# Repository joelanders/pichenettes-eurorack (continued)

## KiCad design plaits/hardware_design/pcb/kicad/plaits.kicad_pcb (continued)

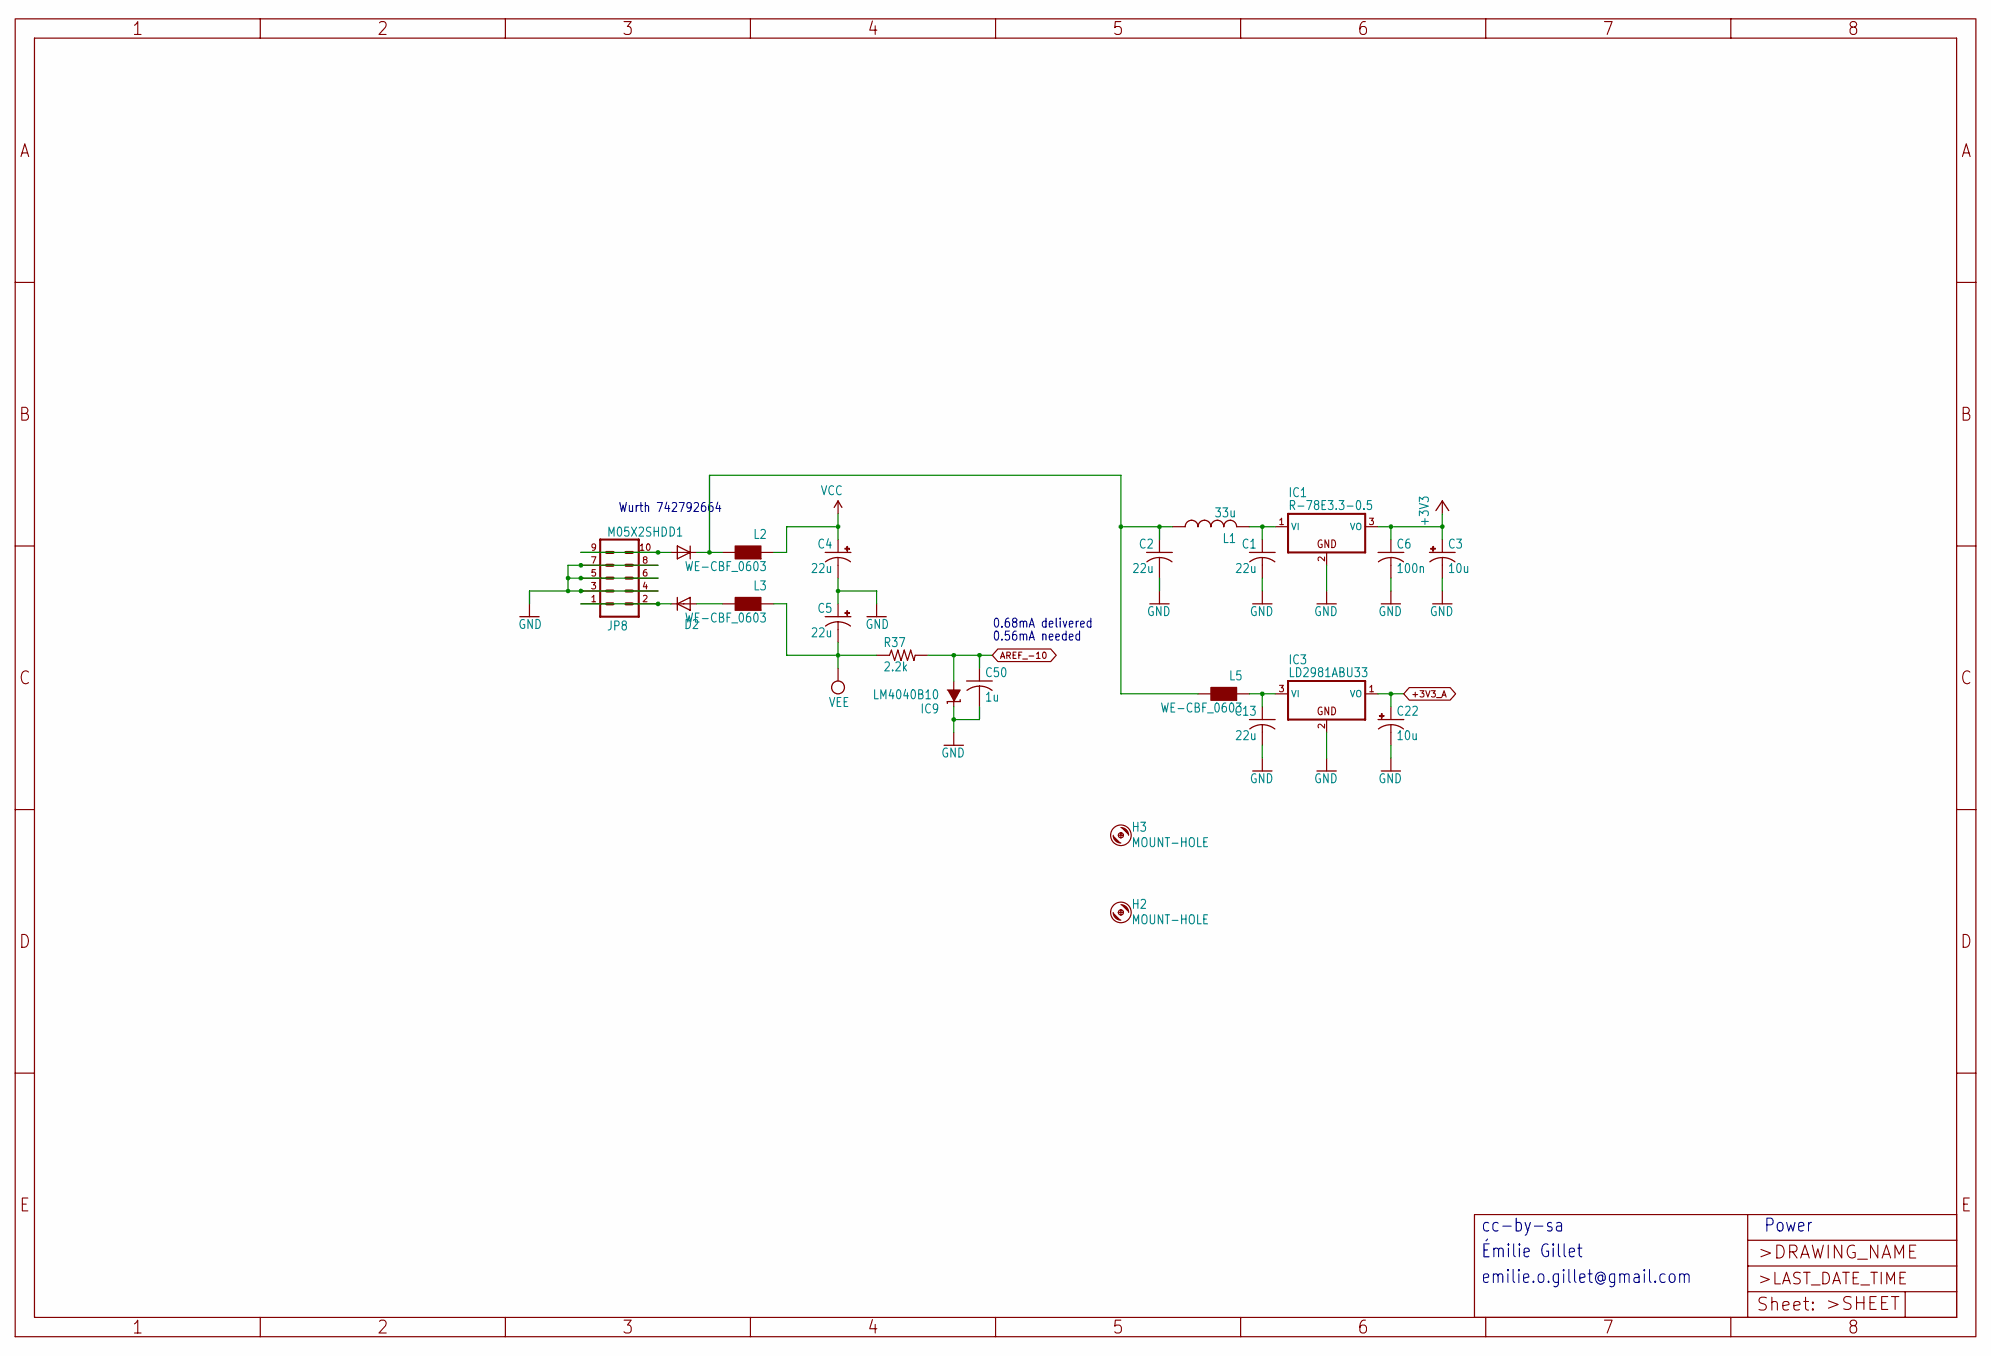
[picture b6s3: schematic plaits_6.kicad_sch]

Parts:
C1, C2, C13: 22u; C1206
C3, C22: 10u; PANASONIC_B
C4, C5: 22u; PANASONIC_B
C6: 100n; C0402
C50: 1u; C0402
D1, D2: 1N5819HW; SOD123
H2, H3: MOUNT-HOLE; 3,0TINY
IC1: R-78E3.3-0.5; WE78
IC3: LD2981ABU33; SOT89
IC9: LM4040B10; DBZ_R-PDSO-G3
JP8: M05X2SHD; 2X5-SHROUDED
L1: 33u; L2012C
L2, L3, L5: WE-CBF_0603; 0603
R37: 2.2k; R0402

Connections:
+3V3: C3.+, C6.1, IC1.3 (VO); also elsewhere on the board
+3V3_A: C22.+, IC3.1 (VO); also elsewhere on the board
AREF_-10: C50.1, IC9.2 (A), R37.2; also elsewhere on the board
GND: C1.2, C2.2, C3.-, C4.-, C5.+, C6.2, C13.2, C22.-, C50.2, IC1.2 (GND), IC3.2 (GND), IC9.1 (C), JP8.3, JP8.4, JP8.5, JP8.6, JP8.7, JP8.8; also elsewhere on the board
unnamed: C2.1, D1.C, L1.1, L2.2, L5.2
unnamed: D1.A, JP8.9, JP8.10
unnamed: D2.A, L3.2
unnamed: D2.C, JP8.1, JP8.2
unnamed: C1.1, IC1.1 (VI), L1.2
unnamed: C13.1, IC3.3 (VI), L5.1
VCC: C4.+, L2.1; also elsewhere on the board
VEE: C5.-, L3.1, R37.1; also elsewhere on the board

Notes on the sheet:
Émilie Gillet
0.56mA needed
Power
0.68mA delivered
emilie.o.gillet@gmail.com
Wurth 742792664
cc-by-sa

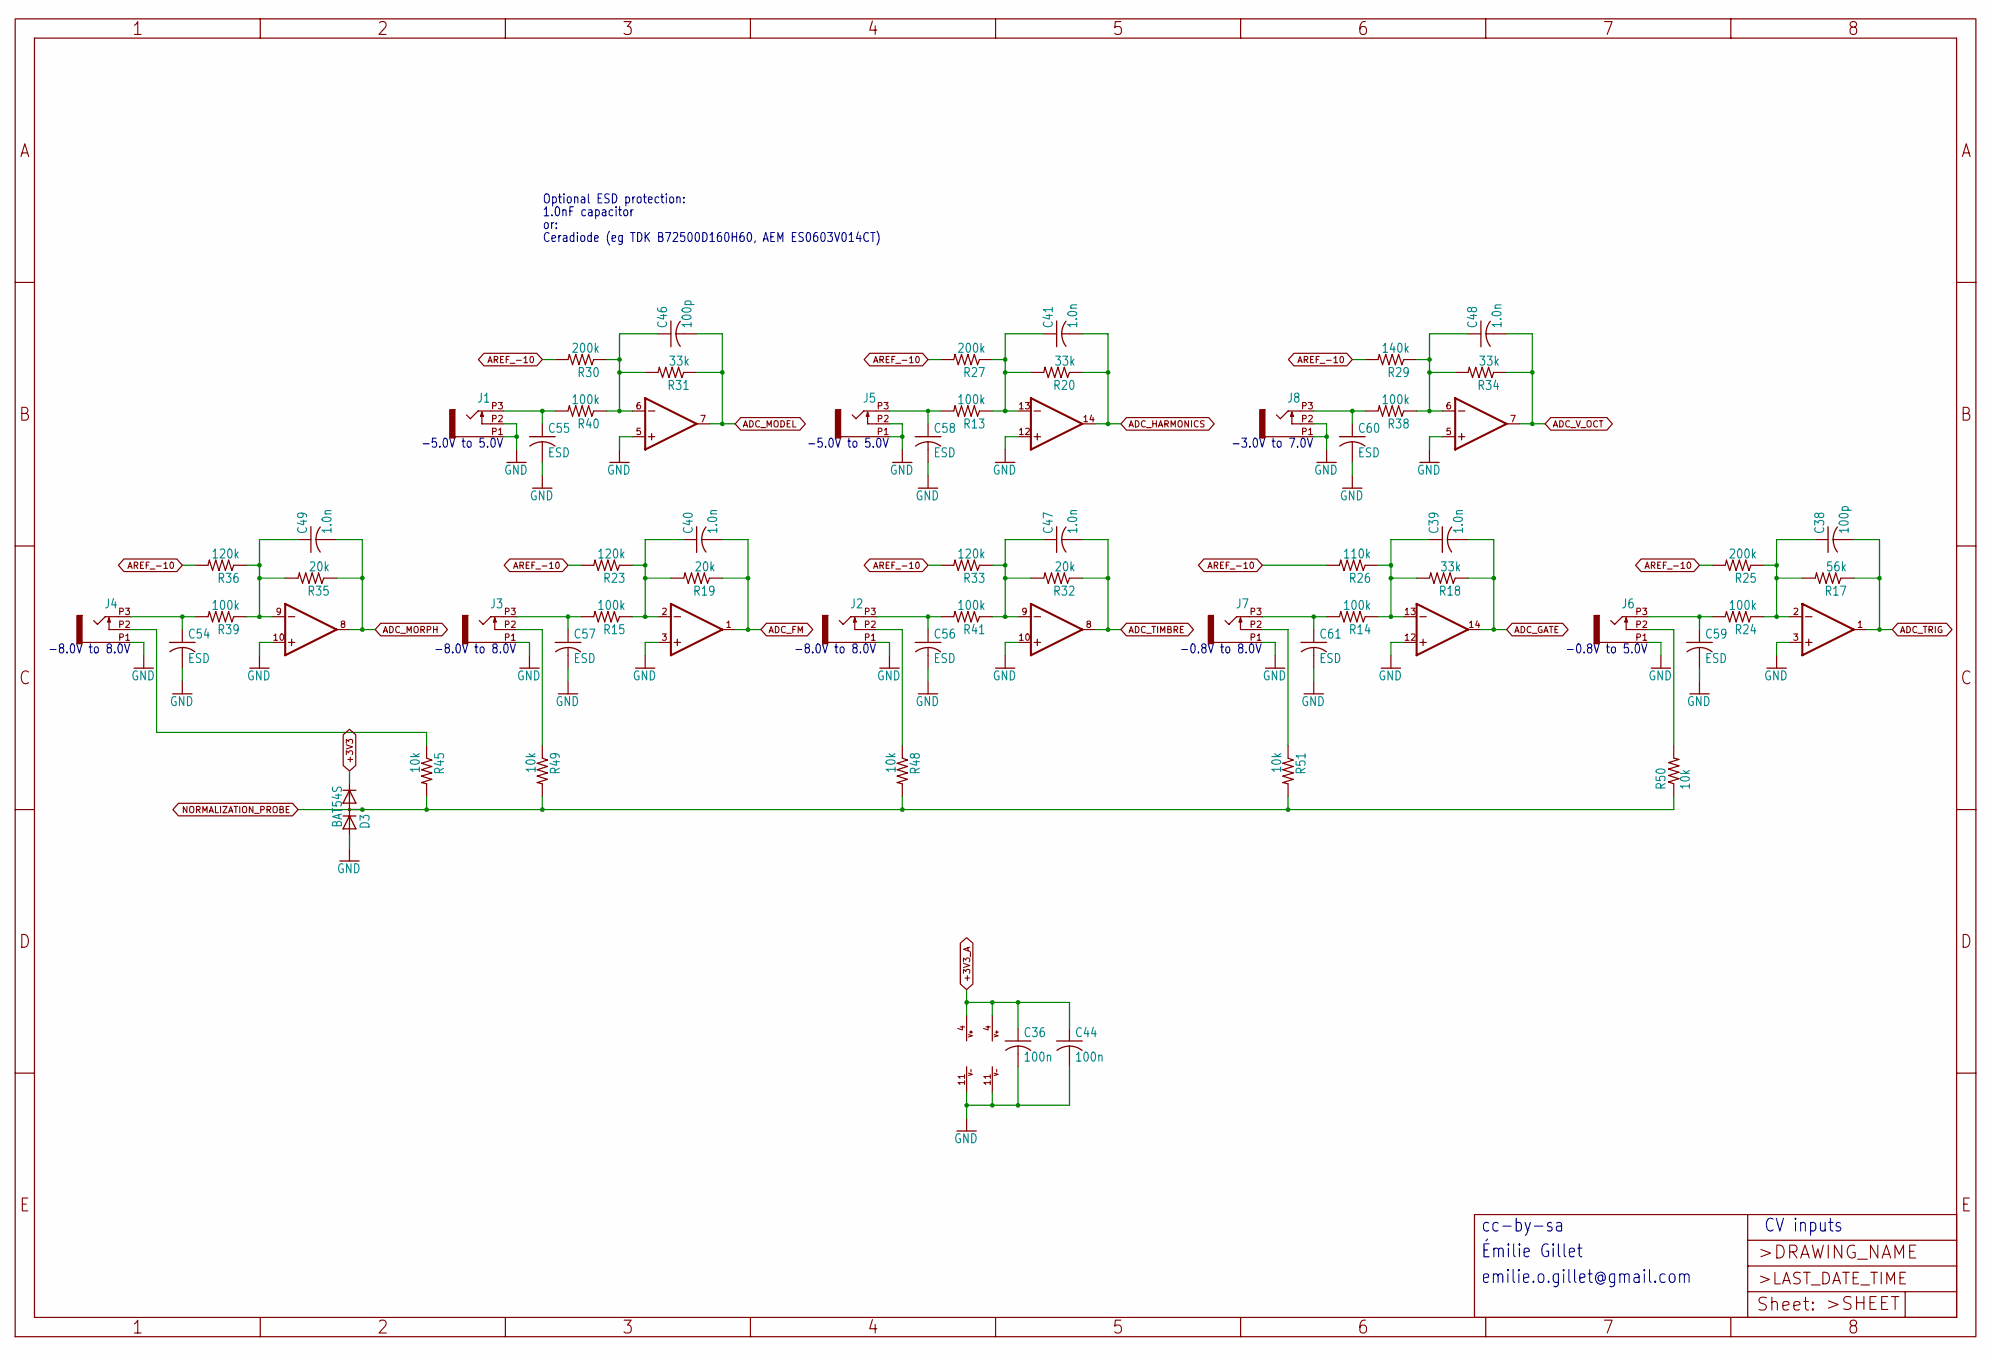
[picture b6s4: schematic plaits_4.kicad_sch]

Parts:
C36, C44: 100n; C0402
C38, C46: 100p; C0402
C39, C40, C41, C47, C48, C49: 1.0n; C0402
C54, C55, C56, C57, C58, C59, C60, C61: ESD; C0603
D3: BAT54S; SOT23
IC6, IC7: MCP6004; TSSOP14_065
J1, J2, J3, J4, J5, J6, J7, J8: PJ301_THONKICONN6; WQP_PJ_301M6
R13, R14, R15, R24, R38, R39, R40, R41: 100k; R0402
R17: 56k; R0402
R18, R20, R31, R34: 33k; R0402
R19, R32, R35: 20k; R0402
R23, R33, R36: 120k; R0402
R25, R27, R30: 200k; R0402
R26: 110k; R0402
R29: 140k; R0402
R45, R48, R49, R50, R51: 10k; R0402

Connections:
+3V3: D3.2 (C); also elsewhere on the board
+3V3_A: C36.1, C44.1, IC6.4 (V+), IC7.4 (V+); also elsewhere on the board
ADC_FM: C40.2, IC7.1 (OUT), R19.1; also elsewhere on the board
ADC_GATE: C39.2, IC6.14 (OUT), R18.1; also elsewhere on the board
ADC_HARMONICS: C41.2, IC7.14 (OUT), R20.1; also elsewhere on the board
ADC_MODEL: C46.2, IC6.7 (OUT), R31.1; also elsewhere on the board
ADC_MORPH: C49.2, IC7.8 (OUT), R35.1; also elsewhere on the board
ADC_TIMBRE: C47.2, IC6.8 (OUT), R32.1; also elsewhere on the board
ADC_TRIG: C38.2, IC6.1 (OUT), R17.1; also elsewhere on the board
ADC_V_OCT: C48.2, IC7.7 (OUT), R34.1; also elsewhere on the board
AREF_-10: R23.2, R25.2, R26.2, R27.2, R29.2, R30.2, R33.2, R36.2; also elsewhere on the board
GND: C36.2, C44.2, C54.2, C55.2, C56.2, C57.2, C58.2, C59.2, C60.2, C61.2, D3.1 (A), IC6.3 (+IN), IC6.5 (+IN), IC6.10 (+IN), IC6.11 (V-), IC6.12 (+IN), IC7.3 (+IN), IC7.5 (+IN), IC7.10 (+IN), IC7.11 (V-), IC7.12 (+IN), J1.P1 (1), J1.P2 (2), J2.P1 (1), J3.P1 (1), J4.P1 (1), J5.P1 (1), J5.P2 (2), J6.P1 (1), J7.P1 (1), J8.P1 (1), J8.P2 (2); also elsewhere on the board
NORMALIZATION_PROBE: D3.3 (AC), R45.2, R48.2, R49.2, R50.1, R51.2; also elsewhere on the board
unnamed: C38.1, IC6.2 (-IN), R17.2, R24.1, R25.1
unnamed: C46.1, IC6.6 (-IN), R30.1, R31.2, R40.1
unnamed: C47.1, IC6.9 (-IN), R32.2, R33.1, R41.1
unnamed: C39.1, IC6.13 (-IN), R14.1, R18.2, R26.1
unnamed: C40.1, IC7.2 (-IN), R15.1, R19.2, R23.1
unnamed: C48.1, IC7.6 (-IN), R29.1, R34.2, R38.1
unnamed: C49.1, IC7.9 (-IN), R35.2, R36.1, R39.1
unnamed: C41.1, IC7.13 (-IN), R13.1, R20.2, R27.1
unnamed: C55.1, J1.P3 (3), R40.2
unnamed: J2.P2 (2), R48.1
unnamed: C56.1, J2.P3 (3), R41.2
unnamed: J3.P2 (2), R49.1
unnamed: C57.1, J3.P3 (3), R15.2
unnamed: J4.P2 (2), R45.1
unnamed: C54.1, J4.P3 (3), R39.2
unnamed: C58.1, J5.P3 (3), R13.2
unnamed: J6.P2 (2), R50.2
unnamed: C59.1, J6.P3 (3), R24.2
unnamed: J7.P2 (2), R51.1
unnamed: C61.1, J7.P3 (3), R14.2
unnamed: C60.1, J8.P3 (3), R38.2

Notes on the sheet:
-0.8V to 8.0V
-0.8V to 5.0V
1.0nF capacitor
-3.0V to 7.0V
Optional ESD protection:
-5.0V to 5.0V
cc-by-sa
or:
Ceradiode (eg TDK B72500D160H60, AEM ES0603V014CT)
-8.0V to 8.0V
CV inputs
Émilie Gillet
emilie.o.gillet@gmail.com

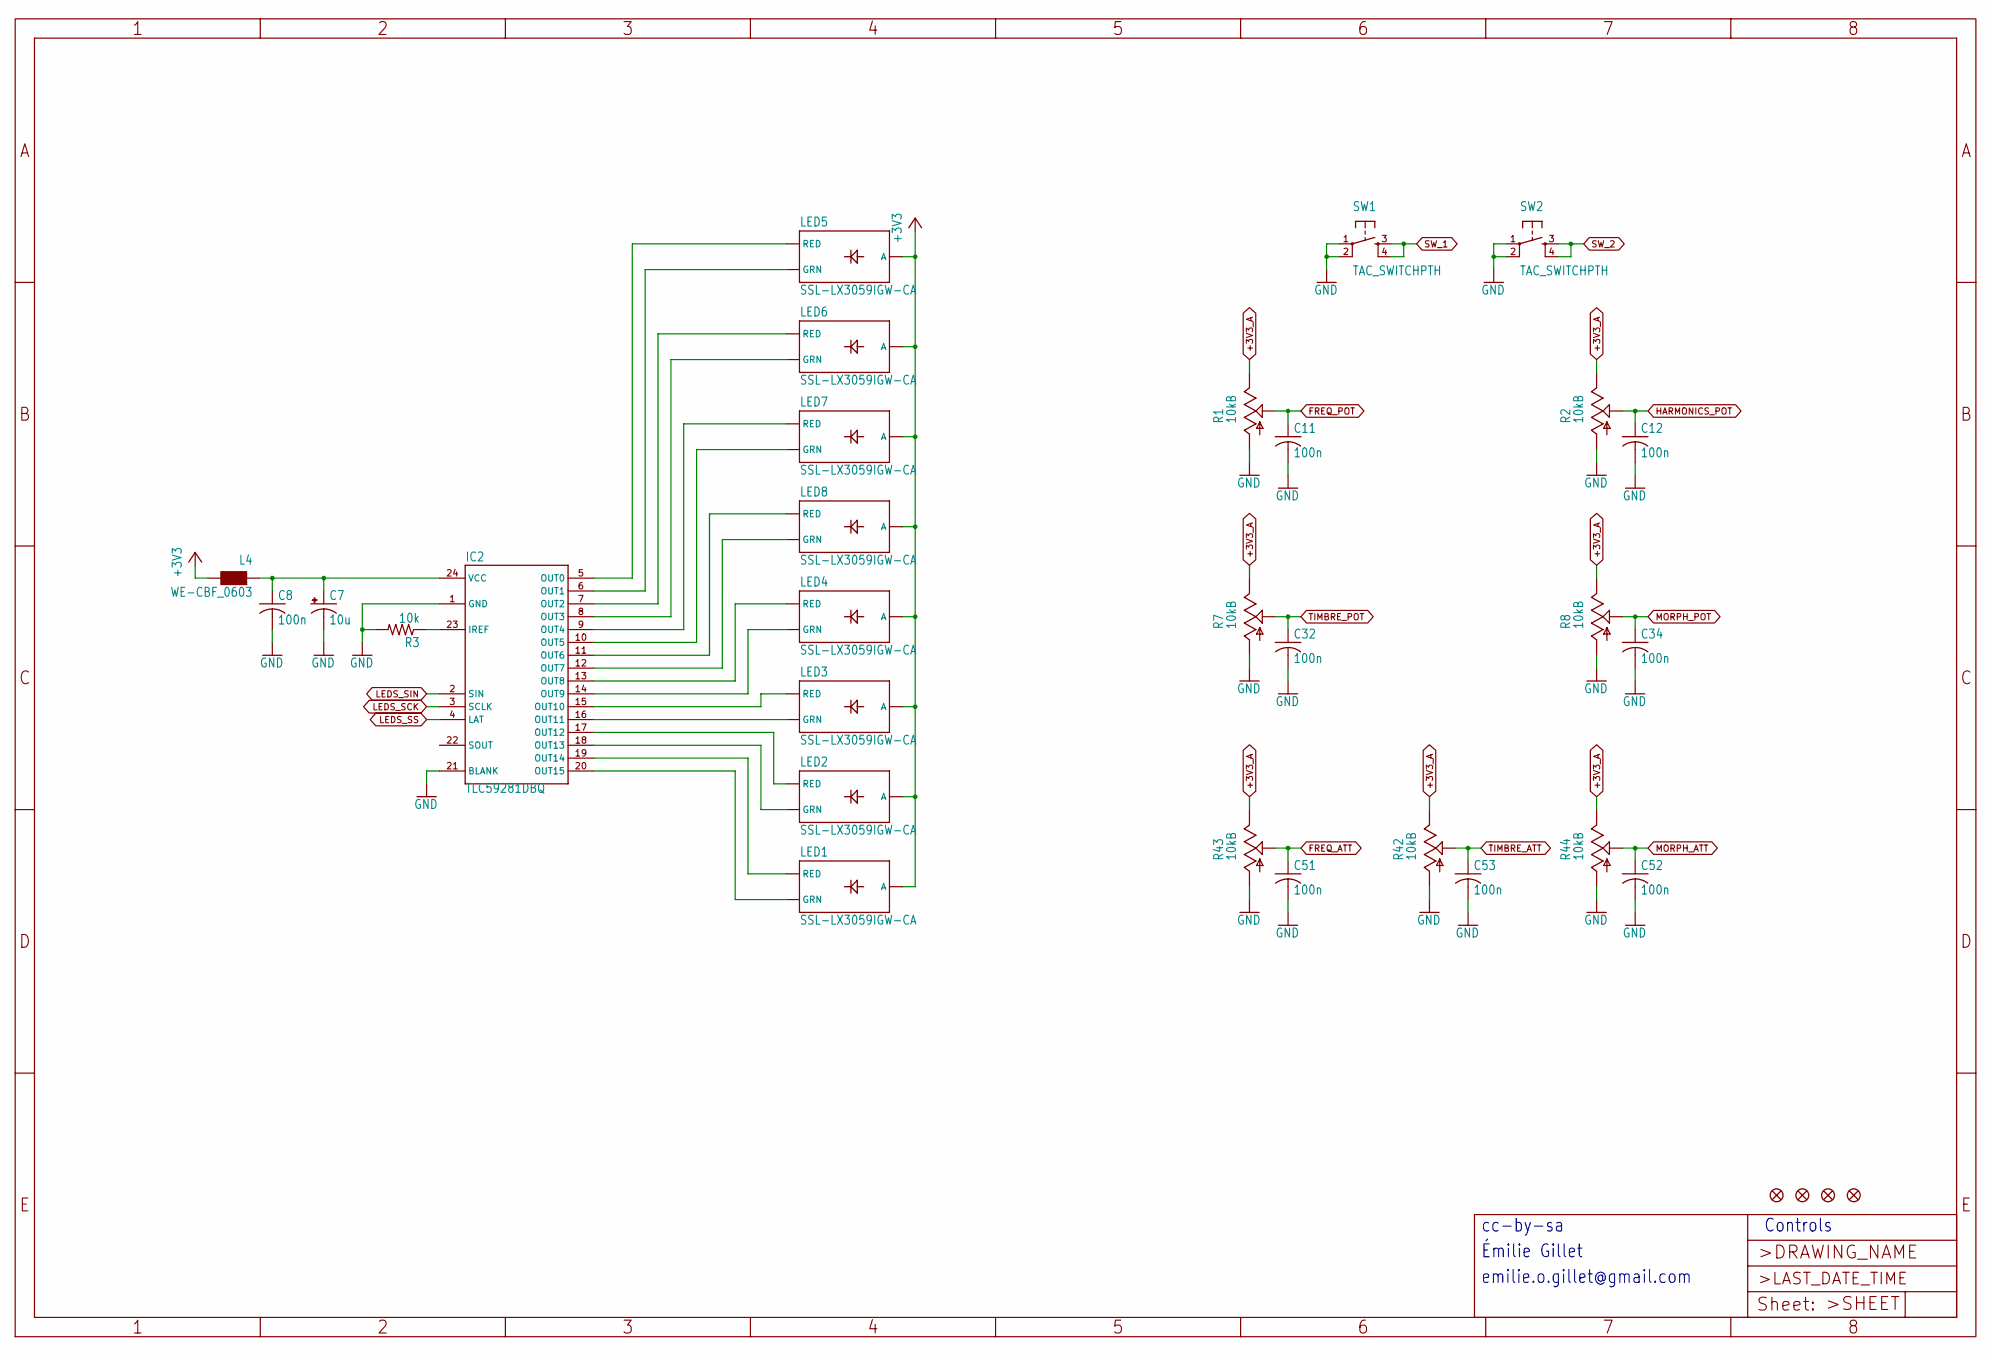
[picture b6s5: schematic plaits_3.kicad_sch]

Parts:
C7: 10u; PANASONIC_B
C8, C11, C12, C32, C34, C51, C52, C53: 100n; C0402
IC2: TLC59281DBQ; TSSOP24_0635
JP1, JP2, JP3, JP4: FIDUCIAL1X2; FIDUCIAL-1X2
L4: WE-CBF_0603; 0603
LED1, LED2, LED3, LED4, LED5, LED6, LED7, LED8: SSL-LX3059IGW-CA; LED-BICOLOR-THROUGHHOLE-LUMEX
R1, R2, R7, R8: 10kB; ALPS_POT_VERTICAL_PS
R3: 10k; R0402
R42, R43, R44: 10kB; ALPS_POT_VERTICAL
SW1, SW2: TAC_SWITCHPTH; TACTILE-PTH

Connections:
+3V3: L4.2, LED1.A, LED2.A, LED3.A, LED4.A, LED5.A, LED6.A, LED7.A, LED8.A; also elsewhere on the board
+3V3_A: R1.P$1 (E), R2.P$1 (E), R7.P$1 (E), R8.P$1 (E), R42.P$1 (E), R43.P$1 (E), R44.P$1 (E); also elsewhere on the board
FREQ_ATT: C51.1, R43.P$2 (S); also elsewhere on the board
FREQ_POT: C11.1, R1.P$2 (S); also elsewhere on the board
GND: C7.-, C8.2, C11.2, C12.2, C32.2, C34.2, C51.2, C52.2, C53.2, IC2.1 (GND), IC2.21 (BLANK), R1.P$3 (A), R2.P$3 (A), R3.2, R7.P$3 (A), R8.P$3 (A), R42.P$3 (A), R43.P$3 (A), R44.P$3 (A), SW1.1, SW1.2, SW2.1, SW2.2; also elsewhere on the board
HARMONICS_POT: C12.1, R2.P$2 (S); also elsewhere on the board
LEDS_SCK: IC2.3 (SCLK); also elsewhere on the board
LEDS_SIN: IC2.2 (SIN); also elsewhere on the board
LEDS_SS: IC2.4 (LAT); also elsewhere on the board
MORPH_ATT: C52.1, R44.P$2 (S); also elsewhere on the board
MORPH_POT: C34.1, R8.P$2 (S); also elsewhere on the board
unnamed: IC2.23 (IREF), R3.1
unnamed: IC2.5 (OUT0), LED5.RED_C (RED)
unnamed: IC2.6 (OUT1), LED5.GREEN_C (GRN)
unnamed: IC2.7 (OUT2), LED6.RED_C (RED)
unnamed: IC2.8 (OUT3), LED6.GREEN_C (GRN)
unnamed: IC2.9 (OUT4), LED7.RED_C (RED)
unnamed: IC2.10 (OUT5), LED7.GREEN_C (GRN)
unnamed: IC2.11 (OUT6), LED8.RED_C (RED)
unnamed: IC2.12 (OUT7), LED8.GREEN_C (GRN)
unnamed: IC2.13 (OUT8), LED4.RED_C (RED)
unnamed: IC2.14 (OUT9), LED4.GREEN_C (GRN)
unnamed: IC2.15 (OUT10), LED3.RED_C (RED)
unnamed: IC2.16 (OUT11), LED3.GREEN_C (GRN)
unnamed: IC2.17 (OUT12), LED2.RED_C (RED)
unnamed: IC2.18 (OUT13), LED2.GREEN_C (GRN)
unnamed: IC2.19 (OUT14), LED1.RED_C (RED)
unnamed: IC2.20 (OUT15), LED1.GREEN_C (GRN)
unnamed: C7.+, C8.1, IC2.24 (VCC), L4.1
SW_1: SW1.3, SW1.4; also elsewhere on the board
SW_2: SW2.3, SW2.4; also elsewhere on the board
TIMBRE_ATT: C53.1, R42.P$2 (S); also elsewhere on the board
TIMBRE_POT: C32.1, R7.P$2 (S); also elsewhere on the board

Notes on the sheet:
emilie.o.gillet@gmail.com
Controls
cc-by-sa
Émilie Gillet

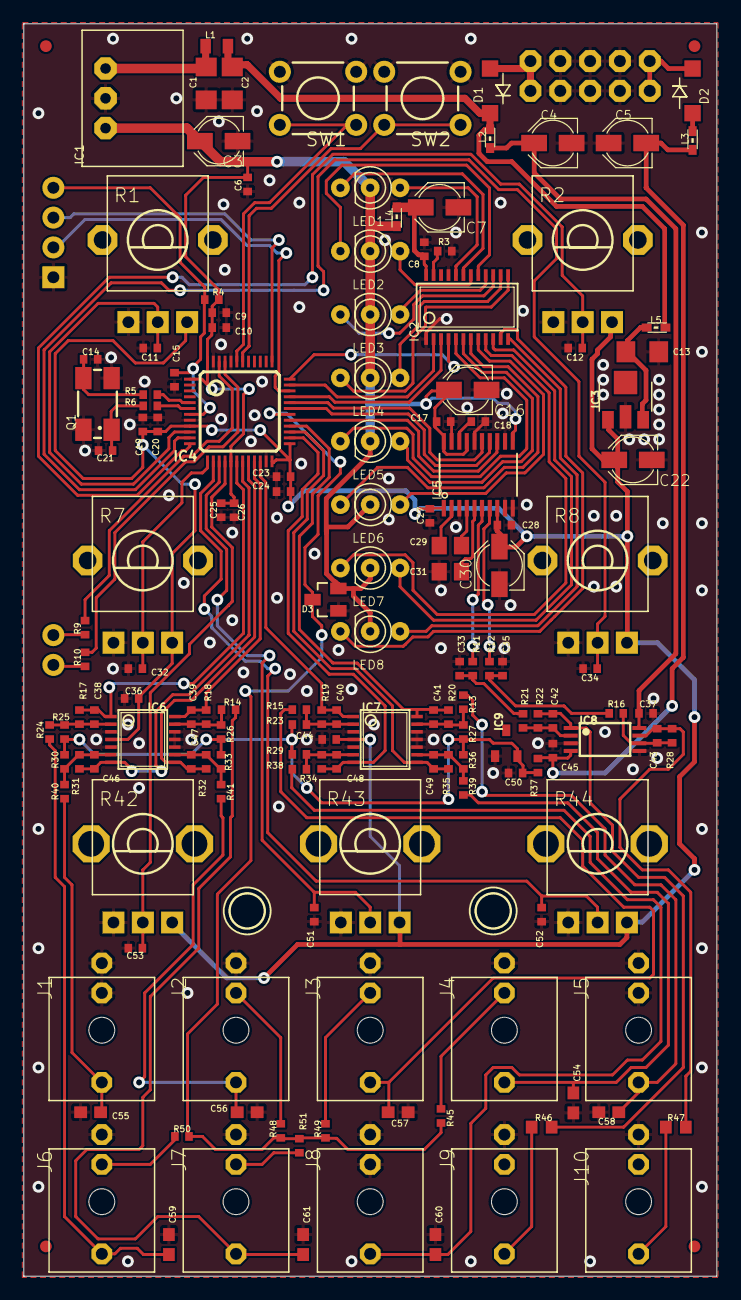
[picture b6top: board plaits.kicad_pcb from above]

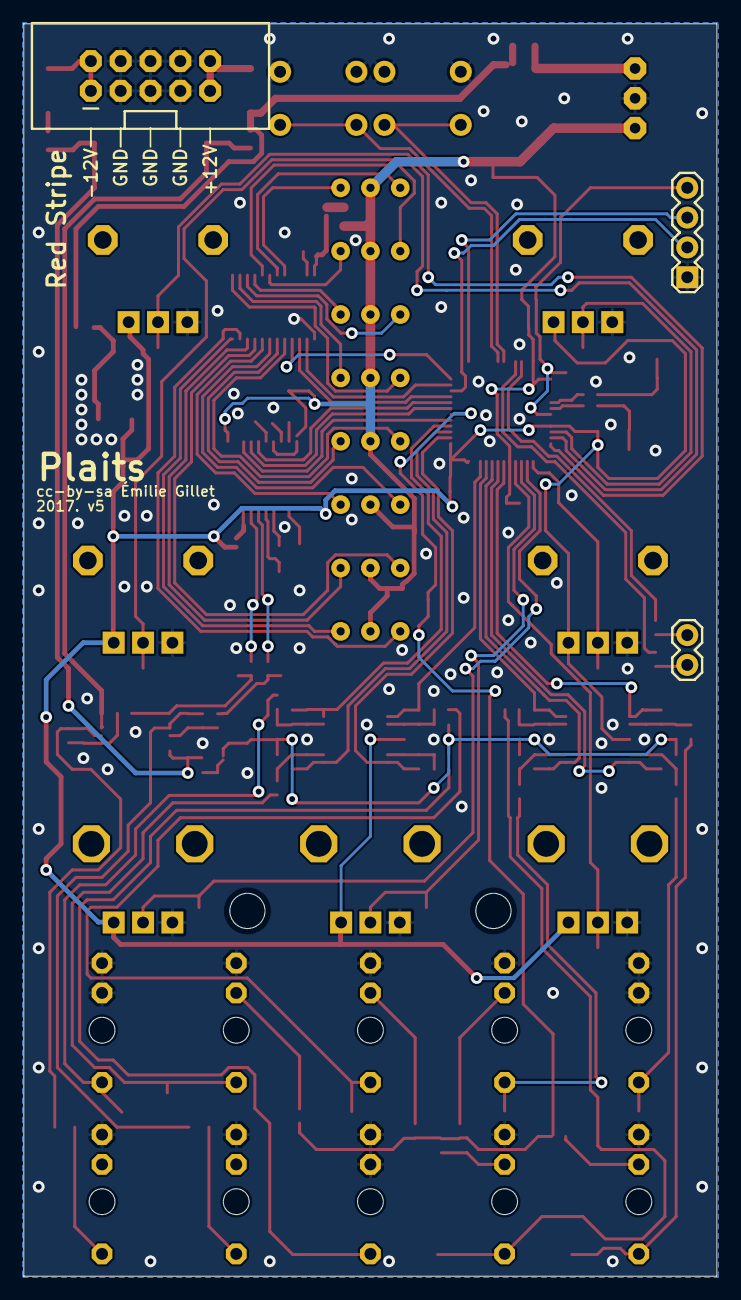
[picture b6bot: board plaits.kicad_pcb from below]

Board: 2 copper layers, 59.0 x 106.7 mm, 159 parts (3 on the bottom side), 100 nets.

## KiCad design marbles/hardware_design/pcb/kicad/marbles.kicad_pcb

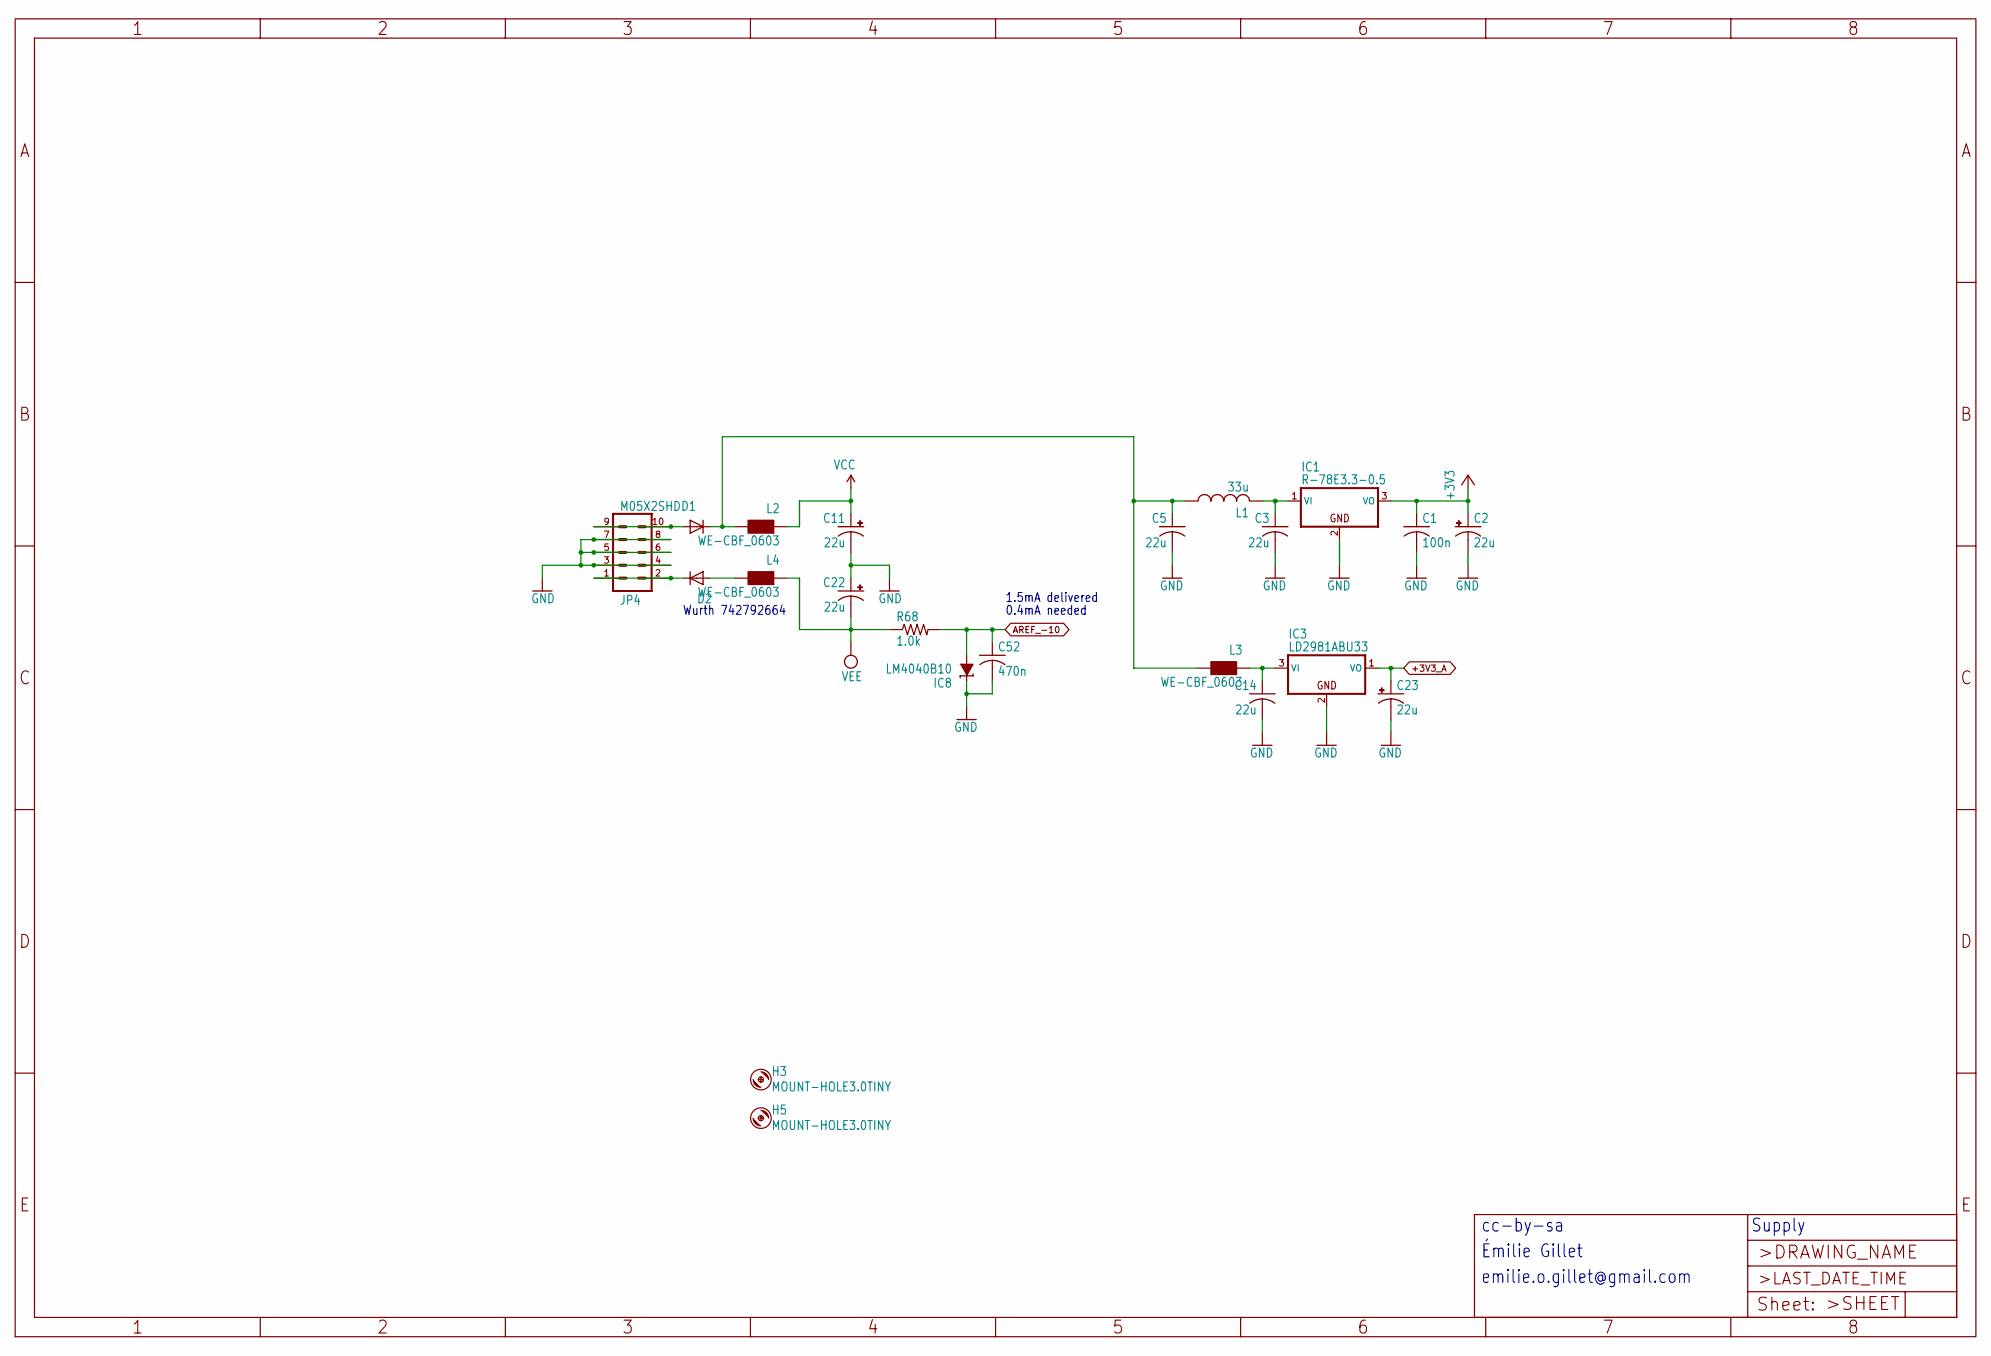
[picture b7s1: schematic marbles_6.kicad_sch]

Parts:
C1: 100n; C0402
C2, C11, C22, C23: 22u; PANASONIC_C
C3, C5, C14: 22u; C1206
C52: 470n; C0402
D1, D2: 1N5819HW; SOD123
H3, H5: MOUNT-HOLE3.0TINY; 3,0TINY
IC1: R-78E3.3-0.5; WE78
IC3: LD2981ABU33; SOT89
IC8: LM4040B10; DBZ_R-PDSO-G3
JP4: M05X2SHD; 2X5-SHROUDED
L1: 33u; L2012C
L2, L3, L4: WE-CBF_0603; 0603
R68: 1.0k; R0402

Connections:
+3V3: C1.1, C2.+, IC1.3 (VO); also elsewhere on the board
+3V3_A: C23.+, IC3.1 (VO); also elsewhere on the board
AREF_-10: C52.1, IC8.2 (A), R68.2; also elsewhere on the board
GND: C1.2, C2.-, C3.2, C5.2, C11.-, C14.2, C22.+, C23.-, C52.2, IC1.2 (GND), IC3.2 (GND), IC8.1 (C), JP4.3, JP4.4, JP4.5, JP4.6, JP4.7, JP4.8; also elsewhere on the board
unnamed: C5.1, D1.C, L1.1, L2.2, L3.2
unnamed: D1.A, JP4.9, JP4.10
unnamed: D2.A, L4.2
unnamed: D2.C, JP4.1, JP4.2
unnamed: C3.1, IC1.1 (VI), L1.2
unnamed: C14.1, IC3.3 (VI), L3.1
VCC: C11.+, L2.1; also elsewhere on the board
VEE: C22.-, L4.1, R68.1; also elsewhere on the board

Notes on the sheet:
Émilie Gillet
emilie.o.gillet@gmail.com
Supply
Wurth 742792664
0.4mA needed
1.5mA delivered
cc-by-sa
